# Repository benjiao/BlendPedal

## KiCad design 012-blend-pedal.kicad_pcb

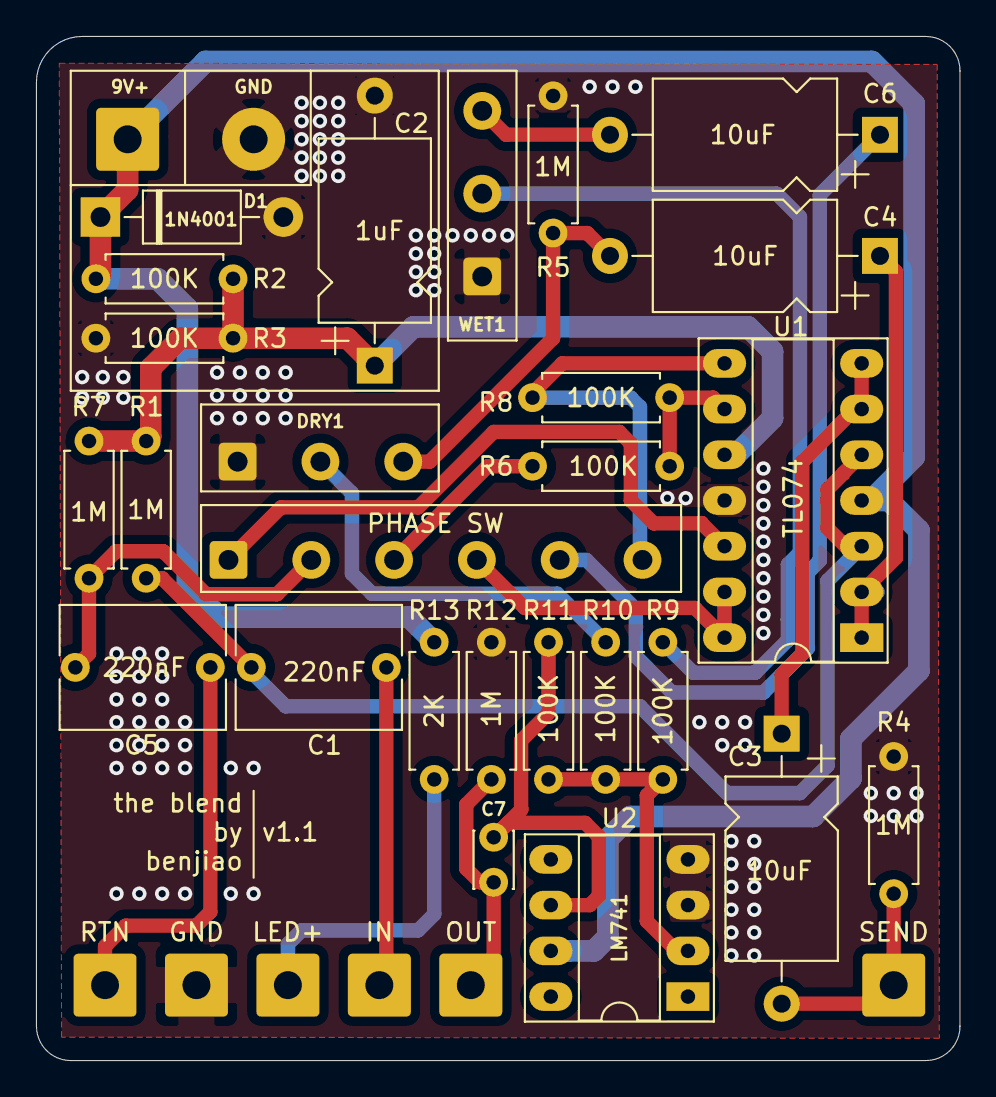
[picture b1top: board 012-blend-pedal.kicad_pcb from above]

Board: 2 copper layers, 51.3 x 56.9 mm, 33 parts (0 on the bottom side), 24 nets.

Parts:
9V+: Jack-DC; SolderWire-0.75sqmm_1x02_P7mm_D1.25mm_OD3.5mm
C1, C5: 220nF; C_Rect_L9.0mm_W6.7mm_P7.50mm_MKT
C2: 1uF; CP_Axial_L10.0mm_D6.0mm_P15.00mm_Horizontal
C3, C4, C6: 10uF; CP_Axial_L10.0mm_D6.0mm_P15.00mm_Horizontal
C7: 100nF; C_Disc_D3.0mm_W2.0mm_P2.50mm
D1: 1N4001; D_DO-41_SOD81_P10.16mm_Horizontal
DRY1: A1M; SolderWire-0.5sqmm_1x03_P4.6mm_D0.9mm_OD2.1mm
GND: GND; SolderWire-0.75sqmm_1x01_D1.25mm_OD3.5mm
IN: INPUT; SolderWire-0.75sqmm_1x01_D1.25mm_OD3.5mm
LED+: LED+; SolderWire-0.75sqmm_1x01_D1.25mm_OD3.5mm
OUT: OUTPUT; SolderWire-0.75sqmm_1x01_D1.25mm_OD3.5mm
PHASE SW: SW_DPDT_x2; SolderWire-0.5sqmm_1x06_P4.6mm_D0.9mm_OD2.1mm
R1, R4, R5, R7, R12: 1M; R_Axial_DIN0207_L6.3mm_D2.5mm_P7.62mm_Horizontal
R2, R3, R6, R8, R9, R10, R11: 100K; R_Axial_DIN0207_L6.3mm_D2.5mm_P7.62mm_Horizontal
R13: 2K; R_Axial_DIN0207_L6.3mm_D2.5mm_P7.62mm_Horizontal
RTN: RETURN; SolderWire-0.75sqmm_1x01_D1.25mm_OD3.5mm
SEND: SEND; SolderWire-0.75sqmm_1x01_D1.25mm_OD3.5mm
U1: TL074; DIP-14_W7.62mm_Socket_LongPads
U2: LM741; DIP-8_W7.62mm_Socket_LongPads
WET1: A1M; SolderWire-0.5sqmm_1x03_P4.6mm_D0.9mm_OD2.1mm

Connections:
+4.5V: C2.1, R1.2, R2.2, R3.1, R7.2, U1.10
+9V: 9V+.1, D1.1, R2.1, R13.1, U1.4, U2.7
GND: 9V+.2, C2.2, D1.2, DRY1.1, GND.1, R3.2, R4.2, R5.2, R12.2, U1.11, U2.3, U2.4, WET1.1
unnamed: C1.1, R1.1, U1.3, U1.5
unnamed: C1.2, IN.1
unnamed: C3.1, U1.6, U1.7
unnamed: C3.2, R4.1, SEND.1
unnamed: C4.1, U1.1, U1.2
unnamed: C4.2, DRY1.3, R5.1
unnamed: C5.1, PHASE SW.2, R7.1
unnamed: C5.2, RTN.1
unnamed: C6.1, PHASE SW.5
unnamed: C6.2, WET1.3
unnamed: C7.1, OUT.1, R12.1
unnamed: C7.2, R11.1, U2.6
unnamed: DRY1.2, R10.2
unnamed: R6.1, R8.2, U1.9
unnamed: PHASE SW.3, R6.2
unnamed: PHASE SW.6, R8.1, U1.8
unnamed: R9.2, WET1.2
unnamed: R9.1, R10.1, R11.2, U2.2
unnamed: LED+.1, R13.2
unnamed: PHASE SW.1, U1.12
unnamed: PHASE SW.4, U1.13, U1.14
